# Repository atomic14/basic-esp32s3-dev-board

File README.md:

# Very Basic ESP32-S3 Dev Board

More details available with this video [here](https://youtu.be/YMnd2NHENCI)

This is a super simple ESP32-S3 Dev Board with the bare mininum required to get it working.

We have:

- USB-C connector with 5.1K pull down resistors on CC1 and CC2
- 3V3 LDO Regulator
- Decoupling Capacitors
- indicated LEDs - 5V, 3V3, GPIO21

Things that we don't have:

- Additonal ESD protection on the USB port
- Battery charging and power path control
- Any exciting peripherals

## Schematic

- View the schematic PDF: [docs/schematic.pdf](docs/schematic.pdf)

## PCB

- 3D Model (STEP): [docs/dev-board.step](docs/dev-board.step)

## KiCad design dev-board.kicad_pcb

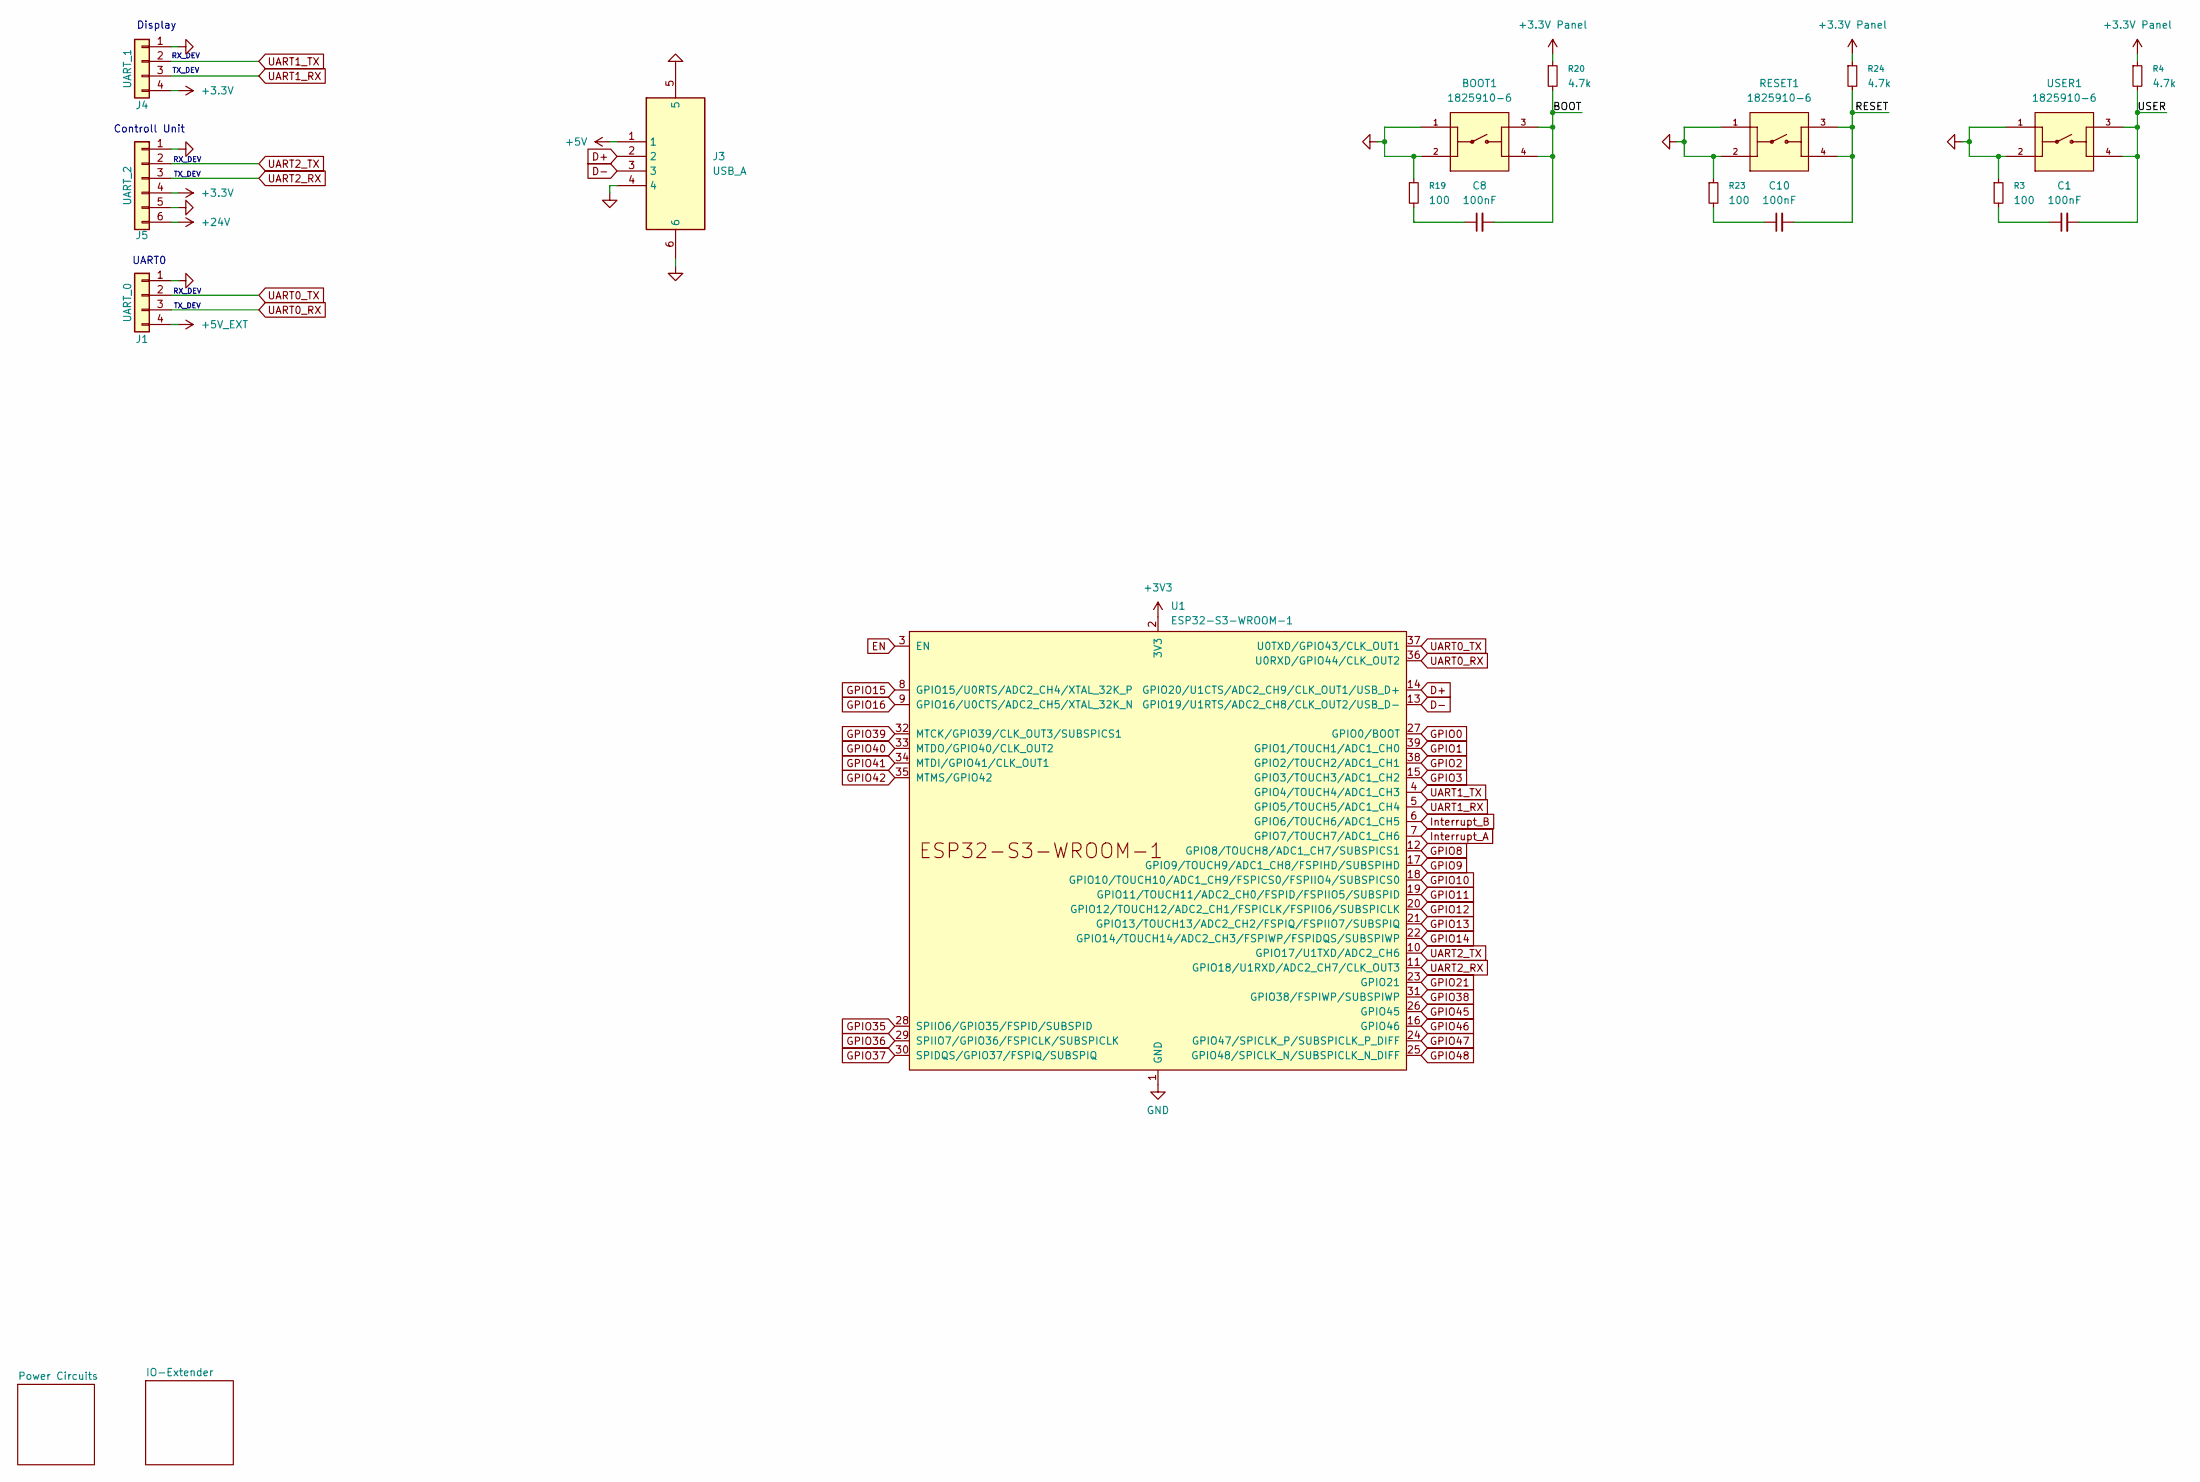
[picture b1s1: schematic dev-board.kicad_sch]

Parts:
BOOT1: 1825910-6; SW_1825910-6-4; PARTREV C10
C1, C8, C10: 100nF; C_1206_3216Metric
J1: UART_0; JST_XH_B4B-XH-A_1x04_P2.50mm_Vertical
J3: USB_A; USB-2.0-TYPE-A; Mouser Part Number 710-614004190021
J4: UART_1; JST_XH_B4B-XH-A_1x04_P2.50mm_Vertical
J5: UART_2; JST_XH_S6B-XH-A-1_1x06_P2.50mm_Horizontal
R3, R19, R23: 100; R_1206_3216Metric
R4, R20, R24: 4.7k; R_1206_3216Metric
RESET1: 1825910-6; SW_1825910-6-4; PARTREV C10
U1: ESP32-S3-WROOM-1
USER1: 1825910-6; SW_1825910-6-4; PARTREV C10

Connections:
+3.3V: J4.4, J5.4; also elsewhere on the board
+3.3V Panel: R4.1, R20.1, R24.1
+3V3: U1.2 (3V3)
+5V_EXT: J1.4
+24V: J5.6; also elsewhere on the board
/BOOT: BOOT1.3, BOOT1.4, C8.2, R20.2
/RESET: C10.2, R24.2, RESET1.3, RESET1.4
/USER: C1.2, R4.2, USER1.3, USER1.4
D+: J3.2, U1.14 (GPIO20/U1CTS/ADC2_CH9/CLK_OUT1/USB_D+)
D-: J3.3, U1.13 (GPIO19/U1RTS/ADC2_CH8/CLK_OUT2/USB_D-)
EN: U1.3 (EN)
GND: J1.1, J3.4, J3.5, J3.6, J4.1, J5.1, J5.5, U1.1 (GND), U1.40 (GND), U1.41 (GND); also elsewhere on the board
GND Panel: BOOT1.1, BOOT1.2, R3.1, R19.1, R23.1, RESET1.1, RESET1.2, USER1.1, USER1.2
GPIO0: U1.27 (GPIO0/BOOT)
GPIO1: U1.39 (GPIO1/TOUCH1/ADC1_CH0)
GPIO2: U1.38 (GPIO2/TOUCH2/ADC1_CH1)
GPIO3: U1.15 (GPIO3/TOUCH3/ADC1_CH2)
GPIO8: U1.12 (GPIO8/TOUCH8/ADC1_CH7/SUBSPICS1)
GPIO9: U1.17 (GPIO9/TOUCH9/ADC1_CH8/FSPIHD/SUBSPIHD)
GPIO10: U1.18 (GPIO10/TOUCH10/ADC1_CH9/FSPICS0/FSPIIO4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)
GPIO11: U1.19 (GPIO11/TOUCH11/ADC2_CH0/FSPID/FSPIIO5/S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)
GPIO12: U1.20 (GPIO12/TOUCH12/ADC2_CH1/FSPICLK/FSPIIO6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)
GPIO13: U1.21 (GPIO13/TOUCH13/ADC2_CH2/FSPIQ/FSPIIO7/S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)
GPIO14: U1.22 (GPIO14/TOUCH14/ADC2_CH3/FSPIWP/FSPIDQS/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)
GPIO15: U1.8 (GPIO15/U0RTS/ADC2_CH4/XTAL_32K_P)
GPIO16: U1.9 (GPIO16/U0CTS/ADC2_CH5/XTAL_32K_N)
GPIO21: U1.23 (GPIO21)
GPIO35: U1.28 (SPIIO6/GPIO35/FSPID/SUBSPID)
GPIO36: U1.29 (SPIIO7/GPIO36/FSPICLK/SUBSPICLK)
GPIO37: U1.30 (SPIDQS/GPIO37/FSPIQ/SUBSPIQ)
GPIO38: U1.31 (GPIO38/FSPIWP/SUBSPIWP)
GPIO39: U1.32 (MTCK/GPIO39/CLK_OUT3/SUBSPICS1)
GPIO40: U1.33 (MTDO/GPIO40/CLK_OUT2)
GPIO41: U1.34 (MTDI/GPIO41/CLK_OUT1)
GPIO42: U1.35 (MTMS/GPIO42)
GPIO45: U1.26 (GPIO45)
GPIO46: U1.16 (GPIO46)
GPIO47: U1.24 (GPIO47/SPICLK_P/SUBSPICLK_P_DIFF)
GPIO48: U1.25 (GPIO48/SPICLK_N/SUBSPICLK_N_DIFF)
Interrupt_A: U1.7 (GPIO7/TOUCH7/ADC1_CH6); also elsewhere on the board
Interrupt_B: U1.6 (GPIO6/TOUCH6/ADC1_CH5); also elsewhere on the board
unnamed: C1.1, R3.2
unnamed: C8.1, R19.2
unnamed: C10.1, R23.2
UART0_RX: J1.3, U1.36 (U0RXD/GPIO44/CLK_OUT2)
UART0_TX: J1.2, U1.37 (U0TXD/GPIO43/CLK_OUT1)
UART1_RX: J4.3, U1.5 (GPIO5/TOUCH5/ADC1_CH4)
UART1_TX: J4.2, U1.4 (GPIO4/TOUCH4/ADC1_CH3)
UART2_RX: J5.3, U1.11 (GPIO18/U1RXD/ADC2_CH7/CLK_OUT3)
UART2_TX: J5.2, U1.10 (GPIO17/U1TXD/ADC2_CH6)

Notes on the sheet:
Display
TX_DEV
RX_DEV
UART0
Controll Unit

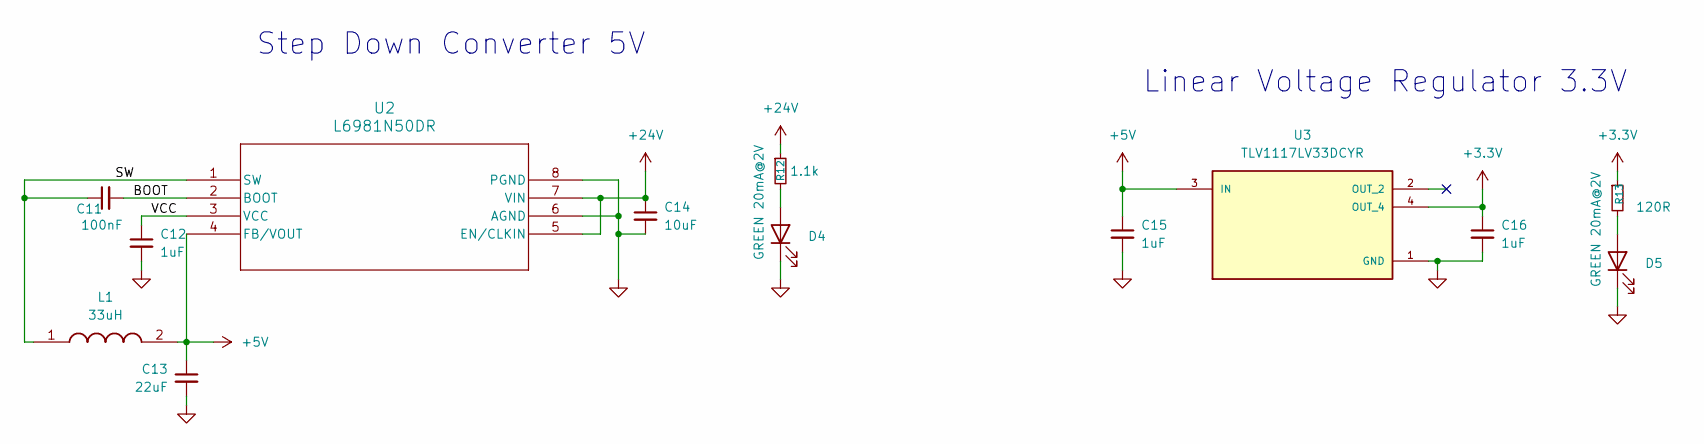
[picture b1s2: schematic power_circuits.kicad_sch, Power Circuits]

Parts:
C11: 100nF; C_1206_3216Metric_Pad1.33x1.80mm_HandSolder
C12, C15, C16: 1uF; C_1206_3216Metric_Pad1.33x1.80mm_HandSolder
C13: 22uF; C_1206_3216Metric_Pad1.33x1.80mm_HandSolder
C14: 10uF; C_1206_3216Metric_Pad1.33x1.80mm_HandSolder
D4, D5: GREEN 20mA@2V; LED_1206_3216Metric_Pad1.42x1.75mm_HandSolder
L1: 33uH; IND_VLS6045EX-330M; Mouser Part Number 810-VLS6045EX-330M
R12: 1.1k; R_1206_3216Metric_Pad1.30x1.75mm_HandSolder
R13: 120R; R_1206_3216Metric_Pad1.30x1.75mm_HandSolder
U2: L6981N50DR; SO8L_L6981N33DR_STM-M
U3: TLV1117LV33DCYR; VREG_TLV1117LV33DCYR; PARTREV B

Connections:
+3.3V: C16.1, R13.1, U3.4 (OUT_4); also elsewhere on the board
+5V: C13.1, C15.1, L1.2, U2.4 (FB/VOUT), U3.3 (IN)
+24V: C14.1, R12.1, U2.5 (EN/CLKIN), U2.7 (VIN); also elsewhere on the board
/Power Circuits/BOOT: C11.2, U2.2 (BOOT)
/Power Circuits/SW: C11.1, L1.1, U2.1 (SW)
/Power Circuits/VCC: C12.1, U2.3 (VCC)
GND: C12.2, C13.2, C14.2, C15.2, C16.2, D4.1 (K), D5.1 (K), U2.6 (AGND), U2.8 (PGND), U3.1 (GND); also elsewhere on the board
unnamed: D4.2 (A), R12.2
unnamed: D5.2 (A), R13.2

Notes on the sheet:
Linear Voltage Regulator 3.3V
Step Down Converter 5V

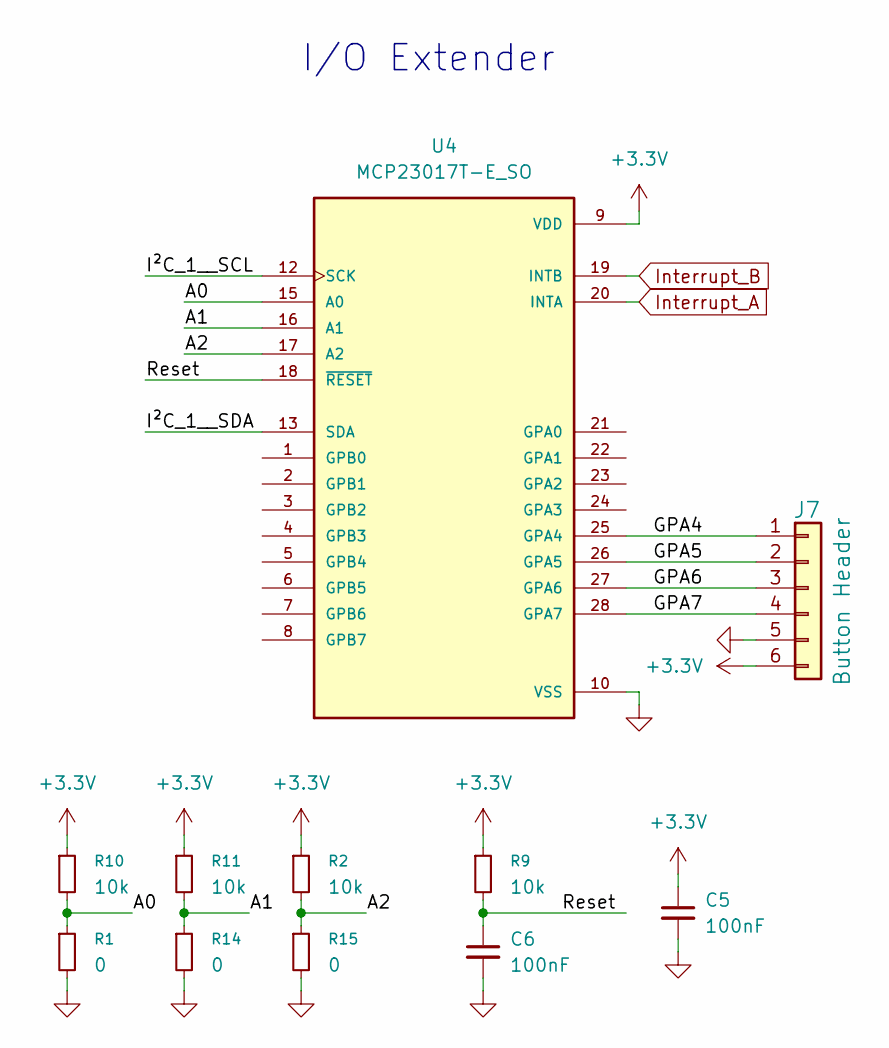
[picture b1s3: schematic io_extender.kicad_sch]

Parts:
C5, C6: 100nF; C_1206_3216Metric
J7: Button Header; JST_PH_B6B-PH-K_1x06_P2.00mm_Vertical
R1, R14, R15: 0; R_1206_3216Metric
R2, R9, R10, R11: 10k; R_1206_3216Metric
U4: MCP23017T-E_SO; SOIC127P1030X265-28N

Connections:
+3.3V: C5.1, J7.6, R2.1, R9.1, R10.1, R11.1, U4.9 (VDD); also elsewhere on the board
/IO-Extender/A0: R1.1, R10.2, U4.15 (A0)
/IO-Extender/A1: R11.2, R14.1, U4.16 (A1)
/IO-Extender/A2: R2.2, R15.1, U4.17 (A2)
/IO-Extender/GPA4: J7.1, U4.25 (GPA4)
/IO-Extender/GPA5: J7.2, U4.26 (GPA5)
/IO-Extender/GPA6: J7.3, U4.27 (GPA6)
/IO-Extender/GPA7: J7.4, U4.28 (GPA7)
/IO-Extender/I²C_1__SCL: U4.12 (SCK)
/IO-Extender/I²C_1__SDA: U4.13 (SDA)
/IO-Extender/Reset: C6.1, R9.2, U4.18 (~RESET)
GND: C5.2, C6.2, J7.5, R1.2, R14.2, R15.2, U4.10 (VSS); also elsewhere on the board
Interrupt_A: U4.20 (INTA); also elsewhere on the board
Interrupt_B: U4.19 (INTB); also elsewhere on the board

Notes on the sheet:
I/O Extender

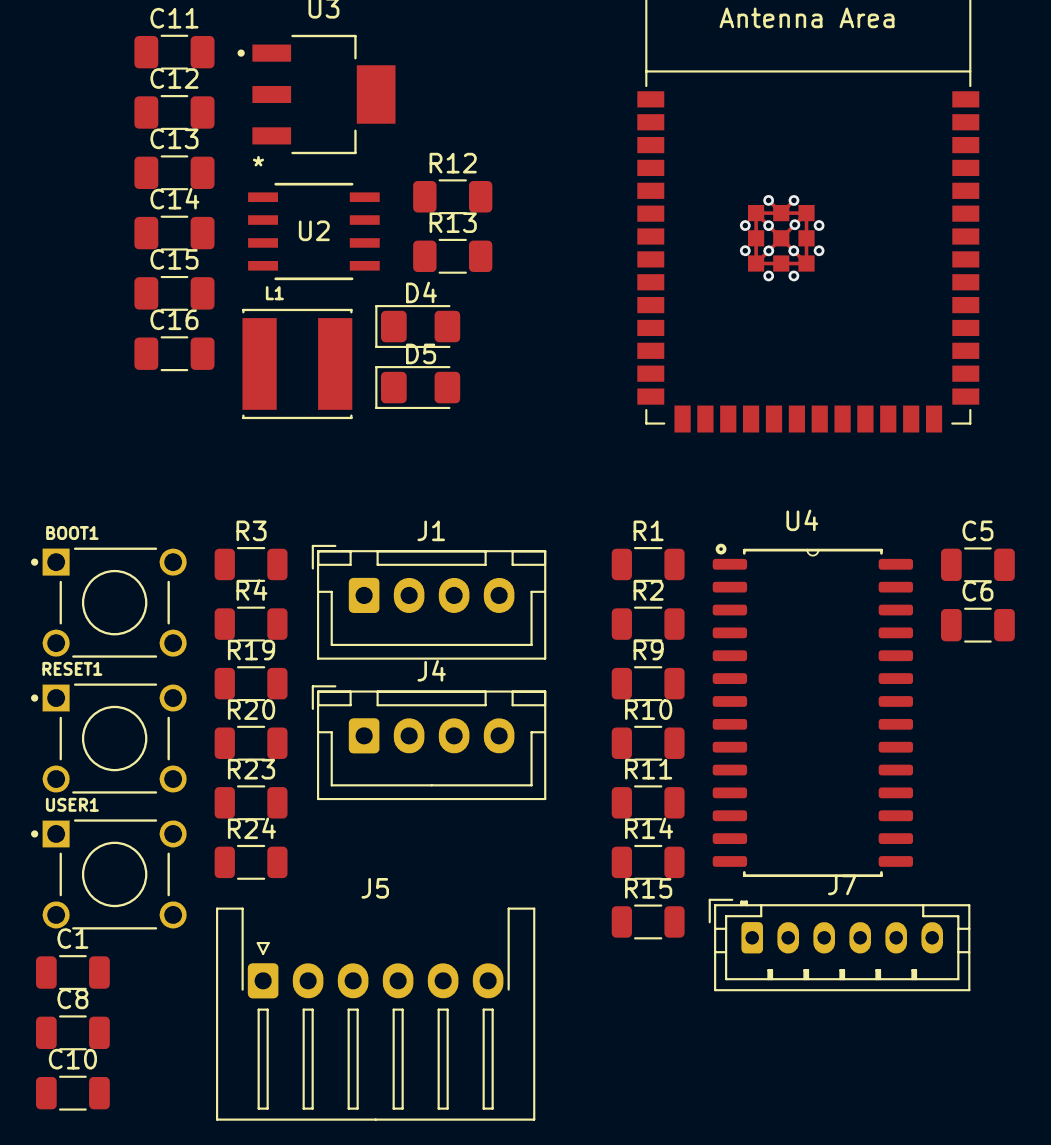
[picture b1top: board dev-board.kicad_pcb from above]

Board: 2 copper layers, 40 parts (0 on the bottom side), 33 nets.

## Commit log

2025-09-19 Github action
2025-09-19 Adds more images to README
2025-09-19 Allow commiting to the docs folder.
2025-09-19 Commit everything in docs
2025-09-19 Fix ordering
2025-09-19 Update docs artifacts (schematic, PCB images, STEP) [skip ci]
2025-09-19 Fix 3d model parths
2025-09-19 nicer 3d export
2025-09-19 Fix path to schematic svg
2025-09-19 Final tweaks
2025-09-19 Last tweaks
2025-09-20 ignore mac files
2025-09-20 Add YouTube video link and thumbnail to README
    Added a YouTube video link and thumbnail to README.
2026-01-14 Minor Changes
2026-01-16 Copy and Adjust Parts from previous version
